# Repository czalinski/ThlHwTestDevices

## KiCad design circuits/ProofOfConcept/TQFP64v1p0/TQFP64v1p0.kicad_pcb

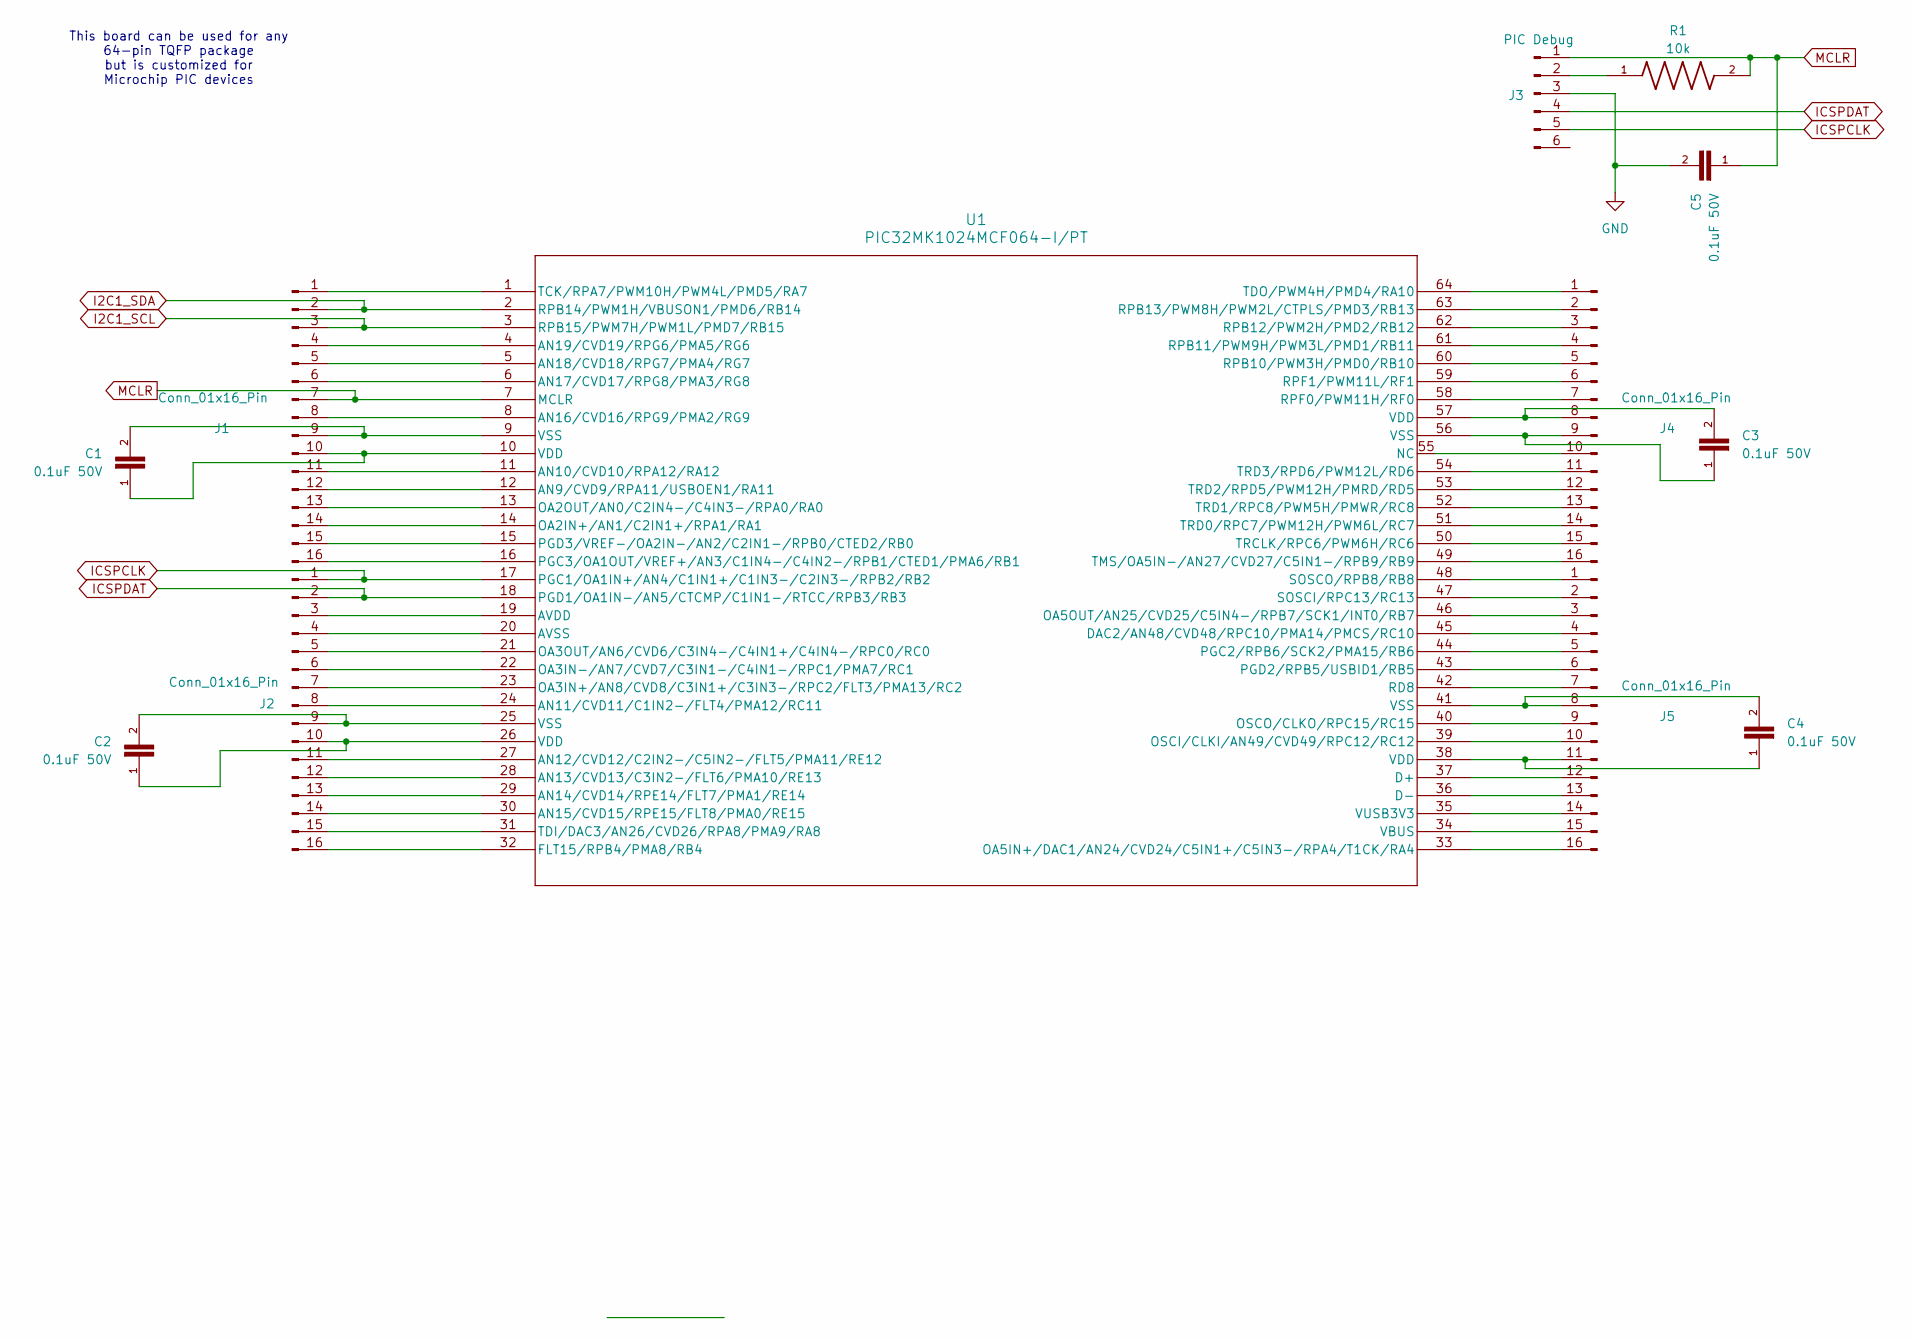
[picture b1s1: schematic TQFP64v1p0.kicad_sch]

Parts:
C1, C2, C3, C4, C5: 0.1uF 50V; CAPC2012X70
J1, J2, J4, J5: Conn_01x16_Pin; PinHeader_1x16_P2.54mm_Vertical
J3: PIC Debug; PinSocket_1x06_P2.54mm_Vertical
R1: 10k; RES_1206
U1: PIC32MK1024MCF064-I/PT; TQFP64_PT_MCH

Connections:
GND: C5.2, J3.3
I2C1_SCL: J1.3, U1.3 (RPB15/PWM7H/PWM1L/PMD7/RB15)
I2C1_SDA: J1.2, U1.2 (RPB14/PWM1H/VBUSON1/PMD6/RB14)
ICSPCLK: J2.1, J3.5, U1.17 (PGC1/OA1IN+/AN4/C1IN1+/C1IN3-/C2IN3-/RP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)
ICSPDAT: J2.2, J3.4, U1.18 (PGD1/OA1IN-/AN5/CTCMP/C1IN1-/RTCC/RPB3/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)
MCLR: C5.1, J1.7, J3.1, R1.2, U1.7 (MCLR)
unnamed: J1.1, U1.1 (TCK/RPA7/PWM10H/PWM4L/PMD5/RA7)
unnamed: J1.4, U1.4 (AN19/CVD19/RPG6/PMA5/RG6)
unnamed: J1.5, U1.5 (AN18/CVD18/RPG7/PMA4/RG7)
unnamed: J1.6, U1.6 (AN17/CVD17/RPG8/PMA3/RG8)
unnamed: J1.8, U1.8 (AN16/CVD16/RPG9/PMA2/RG9)
unnamed: C1.2, J1.9, U1.9 (VSS)
unnamed: C1.1, J1.10, U1.10 (VDD)
unnamed: J1.11, U1.11 (AN10/CVD10/RPA12/RA12)
unnamed: J1.12, U1.12 (AN9/CVD9/RPA11/USBOEN1/RA11)
unnamed: J1.13, U1.13 (OA2OUT/AN0/C2IN4-/C4IN3-/RPA0/RA0)
unnamed: J1.14, U1.14 (OA2IN+/AN1/C2IN1+/RPA1/RA1)
unnamed: J1.15, U1.15 (PGD3/VREF-/OA2IN-/AN2/C2IN1-/RPB0/CTED2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)
unnamed: J1.16, U1.16 (PGC3/OA1OUT/VREF+/AN3/C1IN4-/C4IN2-/RPB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)
unnamed: J2.3, U1.19 (AVDD)
unnamed: J2.4, U1.20 (AVSS)
unnamed: J2.5, U1.21 (OA3OUT/AN6/CVD6/C3IN4-/C4IN1+/C4IN4-/RP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)
unnamed: J2.6, U1.22 (OA3IN-/AN7/CVD7/C3IN1-/C4IN1-/RPC1/PMA7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)
unnamed: J2.7, U1.23 (OA3IN+/AN8/CVD8/C3IN1+/C3IN3-/RPC2/FLT3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)
unnamed: J2.8, U1.24 (AN11/CVD11/C1IN2-/FLT4/PMA12/RC11)
unnamed: C2.2, J2.9, U1.25 (VSS)
unnamed: C2.1, J2.10, U1.26 (VDD)
unnamed: J2.11, U1.27 (AN12/CVD12/C2IN2-/C5IN2-/FLT5/PMA11/RE12)
unnamed: J2.12, U1.28 (AN13/CVD13/C3IN2-/FLT6/PMA10/RE13)
unnamed: J2.13, U1.29 (AN14/CVD14/RPE14/FLT7/PMA1/RE14)
unnamed: J2.14, U1.30 (AN15/CVD15/RPE15/FLT8/PMA0/RE15)
unnamed: J2.15, U1.31 (TDI/DAC3/AN26/CVD26/RPA8/PMA9/RA8)
unnamed: J2.16, U1.32 (FLT15/RPB4/PMA8/RB4)
unnamed: J3.2, R1.1
unnamed: J4.1, U1.64 (TDO/PWM4H/PMD4/RA10)
unnamed: J4.2, U1.63 (RPB13/PWM8H/PWM2L/CTPLS/PMD3/RB13)
unnamed: J4.3, U1.62 (RPB12/PWM2H/PMD2/RB12)
unnamed: J4.4, U1.61 (RPB11/PWM9H/PWM3L/PMD1/RB11)
unnamed: J4.5, U1.60 (RPB10/PWM3H/PMD0/RB10)
unnamed: J4.6, U1.59 (RPF1/PWM11L/RF1)
unnamed: J4.7, U1.58 (RPF0/PWM11H/RF0)
unnamed: C3.2, J4.8, U1.57 (VDD)
unnamed: C3.1, J4.9, U1.56 (VSS)
unnamed: J4.10, U1.55 (NC)
unnamed: J4.11, U1.54 (TRD3/RPD6/PWM12L/RD6)
unnamed: J4.12, U1.53 (TRD2/RPD5/PWM12H/PMRD/RD5)
unnamed: J4.13, U1.52 (TRD1/RPC8/PWM5H/PMWR/RC8)
unnamed: J4.14, U1.51 (TRD0/RPC7/PWM12H/PWM6L/RC7)
unnamed: J4.15, U1.50 (TRCLK/RPC6/PWM6H/RC6)
unnamed: J4.16, U1.49 (TMS/OA5IN-/AN27/CVD27/C5IN1-/RPB9/RB9)
unnamed: J5.1, U1.48 (SOSCO/RPB8/RB8)
unnamed: J5.2, U1.47 (SOSCI/RPC13/RC13)
unnamed: J5.3, U1.46 (OA5OUT/AN25/CVD25/C5IN4-/RPB7/SCK1/INT0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)
unnamed: J5.4, U1.45 (DAC2/AN48/CVD48/RPC10/PMA14/PMCS/RC10)
unnamed: J5.5, U1.44 (PGC2/RPB6/SCK2/PMA15/RB6)
unnamed: J5.6, U1.43 (PGD2/RPB5/USBID1/RB5)
unnamed: J5.7, U1.42 (RD8)
unnamed: C4.2, J5.8, U1.41 (VSS)
unnamed: J5.9, U1.40 (OSCO/CLKO/RPC15/RC15)
unnamed: J5.10, U1.39 (OSCI/CLKI/AN49/CVD49/RPC12/RC12)
unnamed: C4.1, J5.11, U1.38 (VDD)
unnamed: J5.12, U1.37 (D+)
unnamed: J5.13, U1.36 (D-)
unnamed: J5.14, U1.35 (VUSB3V3)
unnamed: J5.15, U1.34 (VBUS)
unnamed: J5.16, U1.33 (OA5IN+/DAC1/AN24/CVD24/C5IN1+/C5IN3-/RP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)

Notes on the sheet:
This board can be used for any 64-pin TQFP package but is customized for Microchip PIC devices

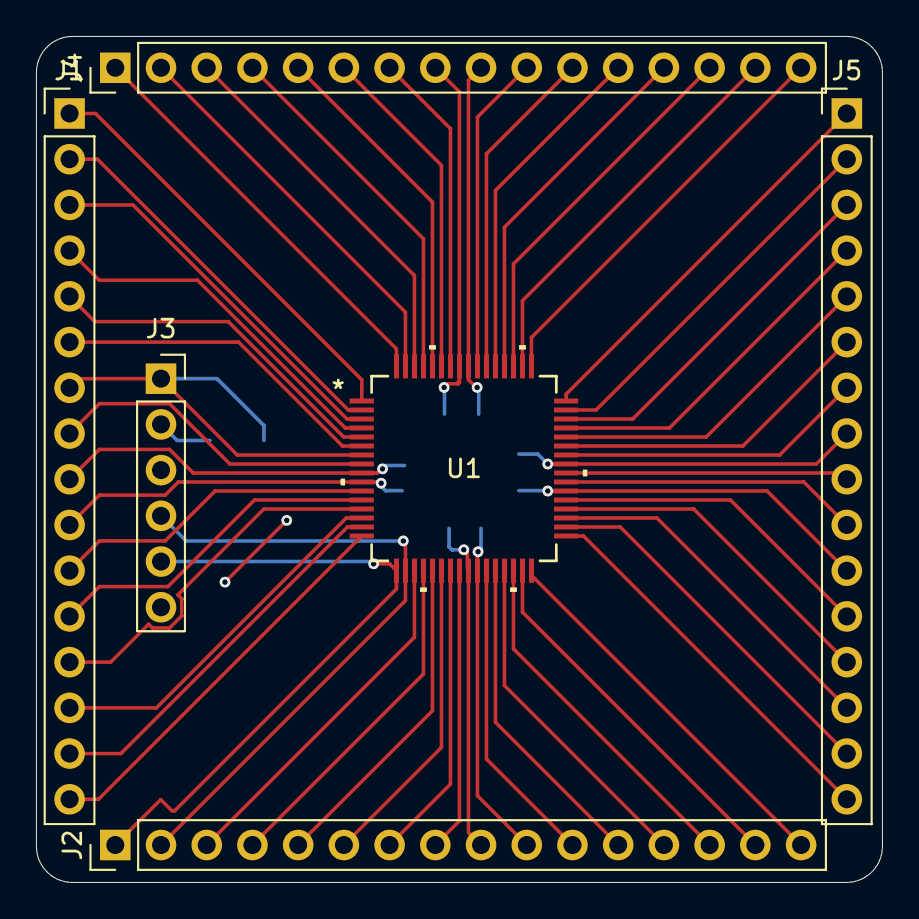
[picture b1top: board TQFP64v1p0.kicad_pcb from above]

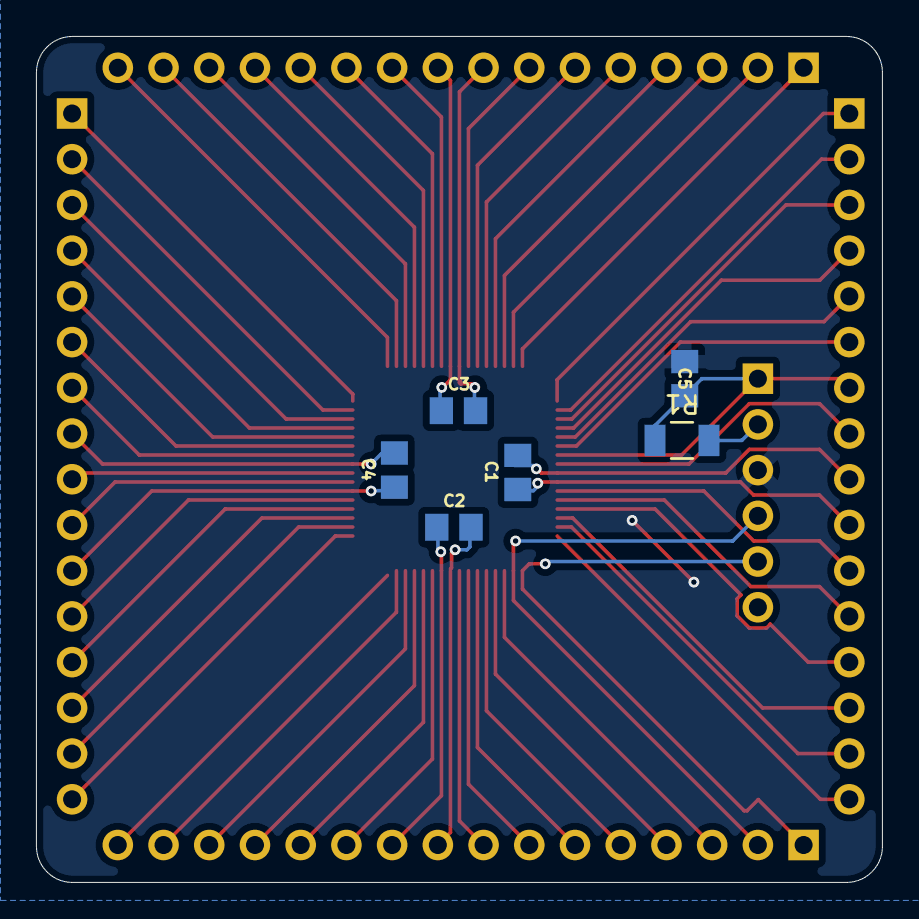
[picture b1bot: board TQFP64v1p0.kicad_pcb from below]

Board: 2 copper layers, 47.0 x 47.0 mm, 12 parts (6 on the bottom side), 66 nets.
